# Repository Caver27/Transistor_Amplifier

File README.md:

# Wzmacniacz tranzystorowy

## Schemat ideowy układu

## Schemat skończonej płytki

## Schemat płytki bez wypełnienia miedzią

## Schematy obudów z własnej biblioteki
| 1804(3314) | CN 15.1 | CN 15.2 |
| :---: | :---: | :---: |
|  |  |  |

## Wykorzystane narzędzia
* Autodesk Eagle 9.6.2
* Własna biblioteka komponentów (folder /libs)

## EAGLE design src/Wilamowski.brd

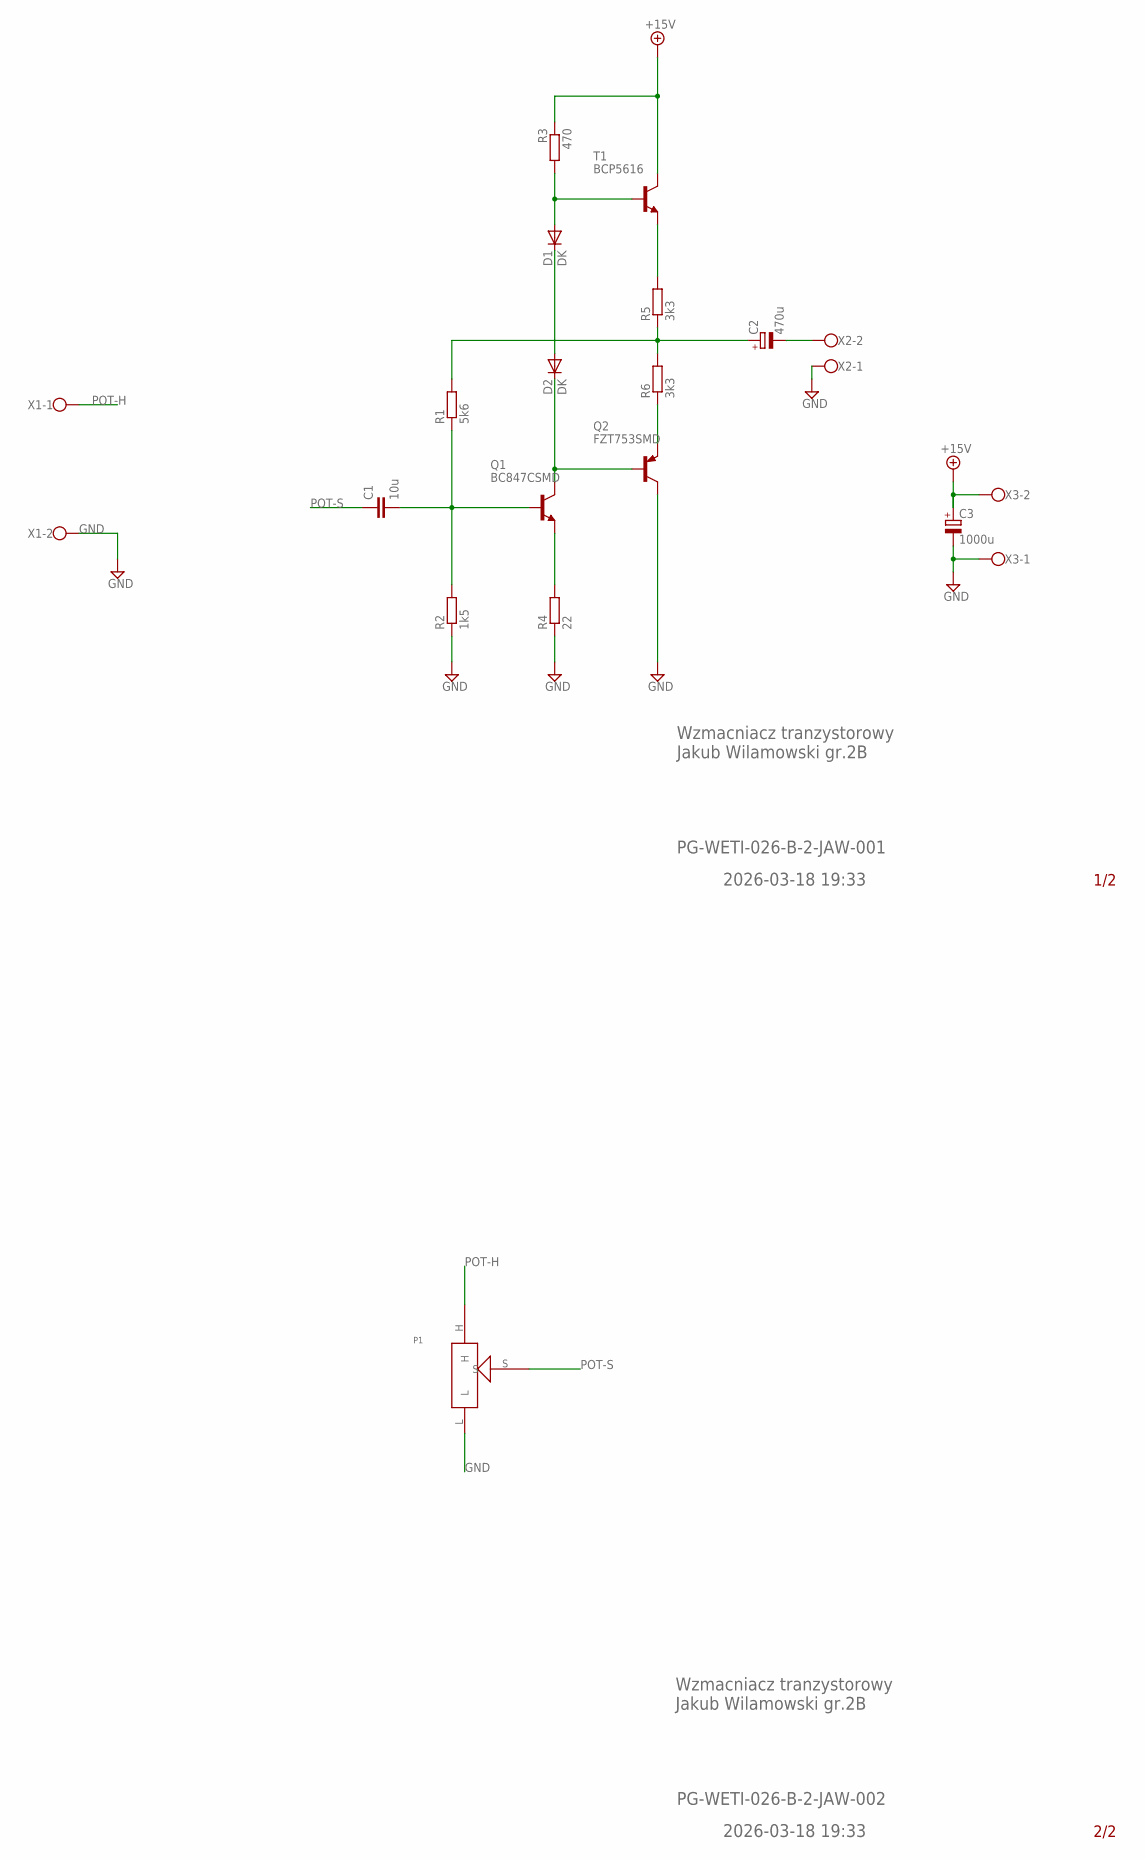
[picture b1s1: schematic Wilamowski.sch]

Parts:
C1: 10u; C025-024X044
C2: 470u; 139CLL-3R
C3: 1000u; 139CLL-3R
D1, D2: DK; SOD106-R
P1: POTENCJOMETRSMD; 1804(3314)
Q1: BC847CSMD; SOT23
Q2: FZT753SMD; SOT223
R1: 5k6; R2010
R2: 1k5; R2010
R3: 470; R2010
R4: 22; R2010
R5, R6: 3k3; R2010
T1: BCP5616; SOT223
X1, X2, X3: W237-102

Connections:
+15V: C3.+, R3.1, T1.4 (C), X3.2
GND: C3.-, P1.L, Q2.2 (C), Q2.4 (C), R2.1, R4.1, X1.2, X2.1, X3.1
unnamed: D2.C, Q1.3 (C), Q2.1 (B)
unnamed: R5.2, T1.3 (E)
unnamed: C2.+, R1.2, R5.1, R6.2
unnamed: Q2.3 (E), R6.1
unnamed: D1.A, R3.2, T1.1 (B)
unnamed: C2.-, X2.2
unnamed: D1.C, D2.A
unnamed: C1.2, Q1.1 (B), R1.1, R2.2
unnamed: Q1.2 (E), R4.2
POT-H: P1.H, X1.1
POT-S: C1.1, P1.S

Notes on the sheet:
1/2
2/2
Wzmacniacz tranzystorowy Jakub Wilamowski gr.2B
PG-WETI-026-B-2-JAW-001
PG-WETI-026-B-2-JAW-002
2026-03-18 19:33

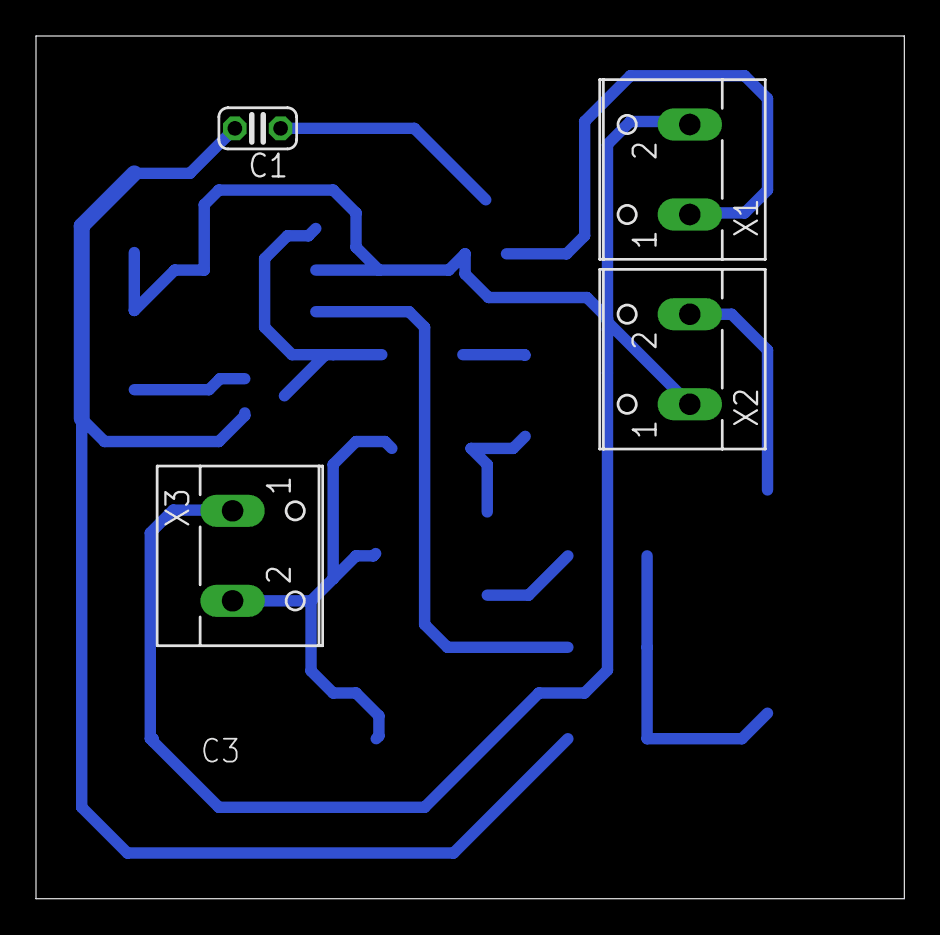
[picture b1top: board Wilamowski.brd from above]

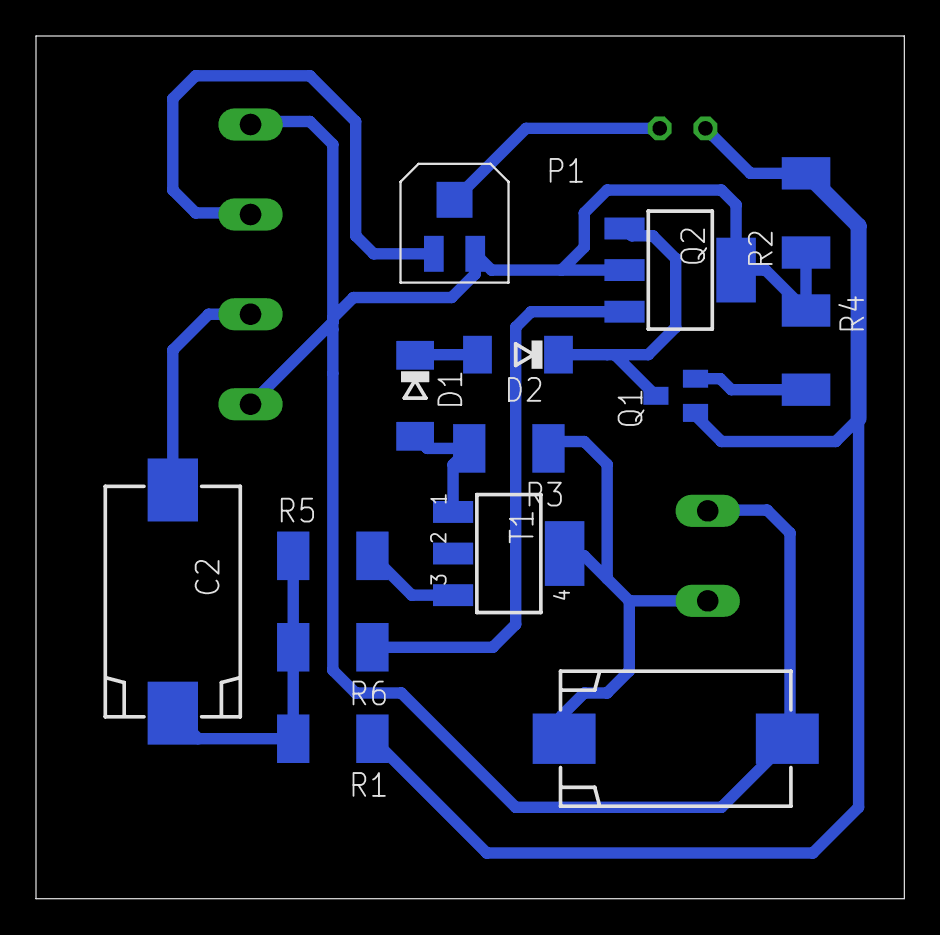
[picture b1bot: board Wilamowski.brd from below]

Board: 2 copper layers, 48.2 x 47.9 mm, 18 parts (14 on the bottom side), 13 nets.

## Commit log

2026-04-08 Projekt PCB wzmacniacza tranzystorowego, jego schemat oraz biblioteka
2026-04-08 Przeniesienie dokumentacji PDF do folderu docs
2026-04-08 Dodano obraz PCB z wypełnieniem miedzią
2026-04-08 Dodano readme
2026-04-08 Zaaktualizowano README
2026-04-08 Create LICENSE
